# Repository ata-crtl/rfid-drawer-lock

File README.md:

# RFID Drawer Lock

A simple NFC drawer lock built using an ESP32-C3, PN532 NFC reader, and an SG90 servo.

I made this because I wanted a way to lock a drawer without dealing with keys or drilling into furniture , i always seem to lose my keys and lock myself out :( . Just tap an authorised NFC card to unlock it, and tap again to lock it.

**Onshape link:**  
[View the Onshape model](https://cad.onshape.com/documents/10ff17bd51048845f2315452/w/f69d7bc4221a2a5968c6b8fb/e/c57b2dc210264a0650e04200?renderMode=0&uiState=6a241e387df4bc474adedac2)

---

## What it does

- Unlocks a drawer using an NFC card or tag  
- Locks again when the same card is tapped  
- Runs on battery so there are no wires going into the drawer  
- Charges via USB using a TP4056 module  
- Uses red and green LEDs for status  
- Has a physical switch to turn everything off  

---

## How it works

The PN532 reads the UID from an NFC card.

The ESP32 checks if that UID matches the one stored in memory. If it matches, the SG90 servo moves the locking mechanism.

There is also a button for setup so you can register a card easily.

---

## Hardware

### Parts Used

- ESP32 DevKitM1 for the main controller  
- PN532 NFC module for reading cards  
- SG90 servo to move the lock  
- TP4056 module for charging the battery  
- 1S LiPo battery for power  
- Slide switch for power control  
- Red LED for locked or error indication  
- Green LED for power indication  
- 330Ω resistors (x2) for LED current limiting  

---
---

## Building

### 1. Assemble the hardware

- Solder headers and connectors onto the PCB  
- Connect the PN532 module  
- Connect the servo  
- Connect the TP4056 charger  
- Plug in the battery  
- Fit everything into the 3D printed enclosure  

### 2. Upload the firmware

```bash
git clone https://github.com/yourusername/rfid-drawer-lock
cd rfid-drawer-lock
```

Open the project in Arduino IDE or PlatformIO and upload it to the ESP32.

### 3. Register a card

- Hold the register button  
- Tap your NFC card  
- Wait for confirmation  
- The card is now linked to the lock  

---

## Installation

The enclosure is made to stick to the inside of a drawer using strong double-sided tape.

The NFC reader sits behind the drawer front , in a little pocket so you can scan cards from outside.

- Double check battery polarity before connecting  
- Power the servo from 5V, not 3.3V  
- Check PN532 mode 
---

## Future improvements

- Support for multiple authorised cards  
- WiFi logging  
- Battery level monitoring  
- Improved enclosure design  
- Buzzer feedback  
- Mobile app integration

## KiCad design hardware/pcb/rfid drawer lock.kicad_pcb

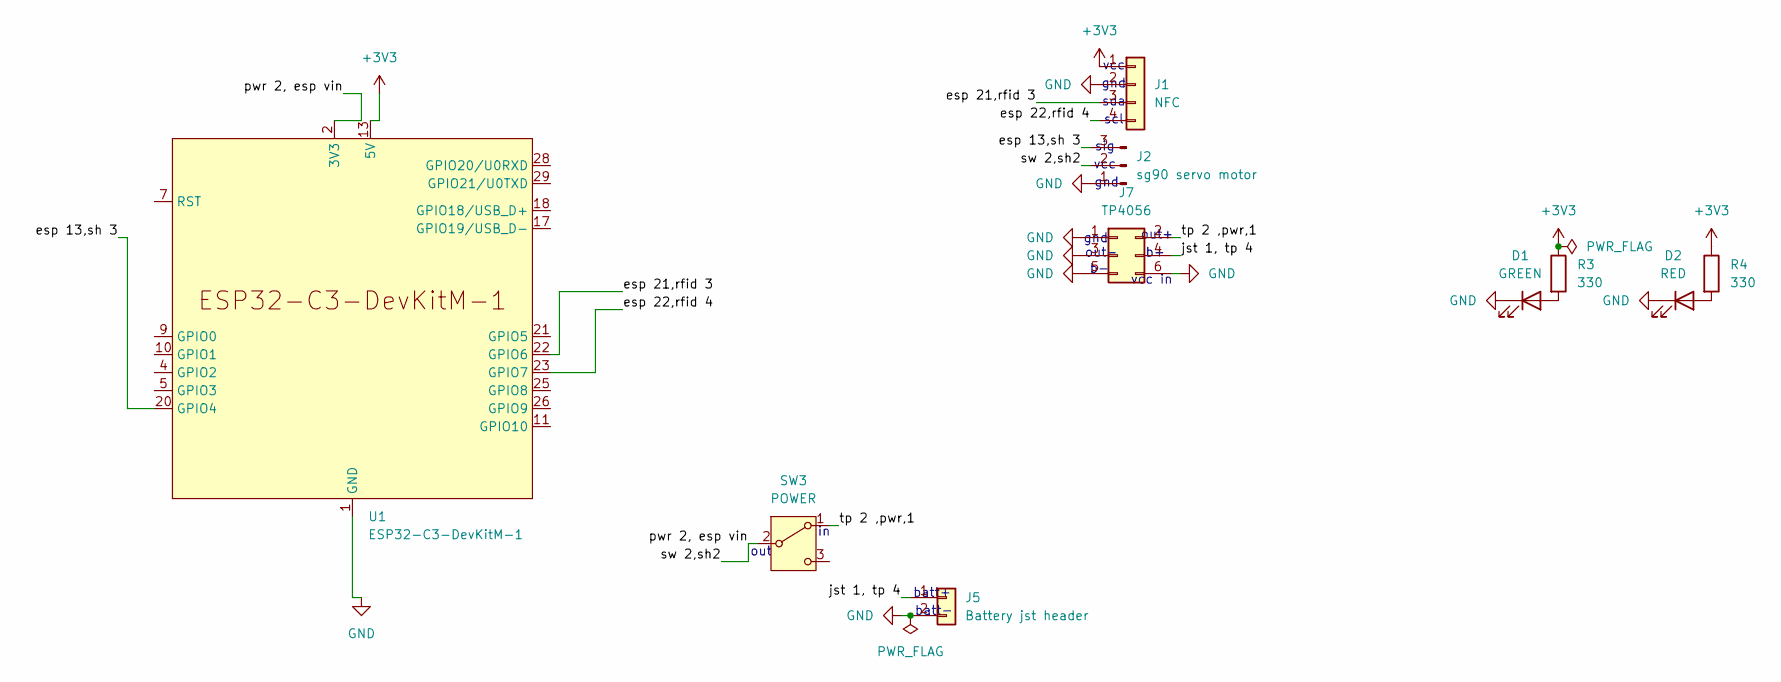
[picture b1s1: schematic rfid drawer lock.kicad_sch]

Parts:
D1: GREEN; LED_D3.0mm
D2: RED; LED_D3.0mm
J1: NFC; PinHeader_1x04_P2.54mm_Vertical
J2: sg90 servo motor; FanPinHeader_1x03_P2.54mm_Vertical
J5: Battery jst header; PinHeader_1x02_P2.54mm_Vertical
J7: TP4056; PinHeader_1x06_P2.54mm_Vertical
R3, R4: 330; R_0805_2012Metric
SW3: POWER; SW_Slide_SPDT_Angled_CK_OS102011MA1Q
U1: ESP32-C3-DevKitM-1

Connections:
3V3: J2.2, SW3.2 (B), U1.2 (3V3), U1.3 (3V3)
+3V3: J1.1, R3.1, R4.1, U1.13 (5V), U1.14 (5V)
/esp 13,sh 3: J2.3, U1.20 (GPIO4)
/esp 21,rfid 3: J1.3, U1.22 (GPIO6)
/esp 22,rfid 4: J1.4, U1.23 (GPIO7)
/jst 1, tp 4: J5.1, J7.4
/tp 2 ,pwr,1: J7.2, SW3.1 (A)
GND: D1.1 (K), D2.1 (K), J1.2, J2.1, J5.2, J7.1, J7.3, J7.5, J7.6, U1.1 (GND), U1.6 (GND), U1.8 (GND), U1.12 (GND), U1.15 (GND), U1.16 (GND), U1.19 (GND), U1.24 (GND), U1.27 (GND), U1.30 (GND)
unnamed: D1.2 (A), R3.2
unnamed: D2.2 (A), R4.2

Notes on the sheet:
sda
out
scl
sig
batt+
vcc
out+
vcc in
gnd
out-
batt-

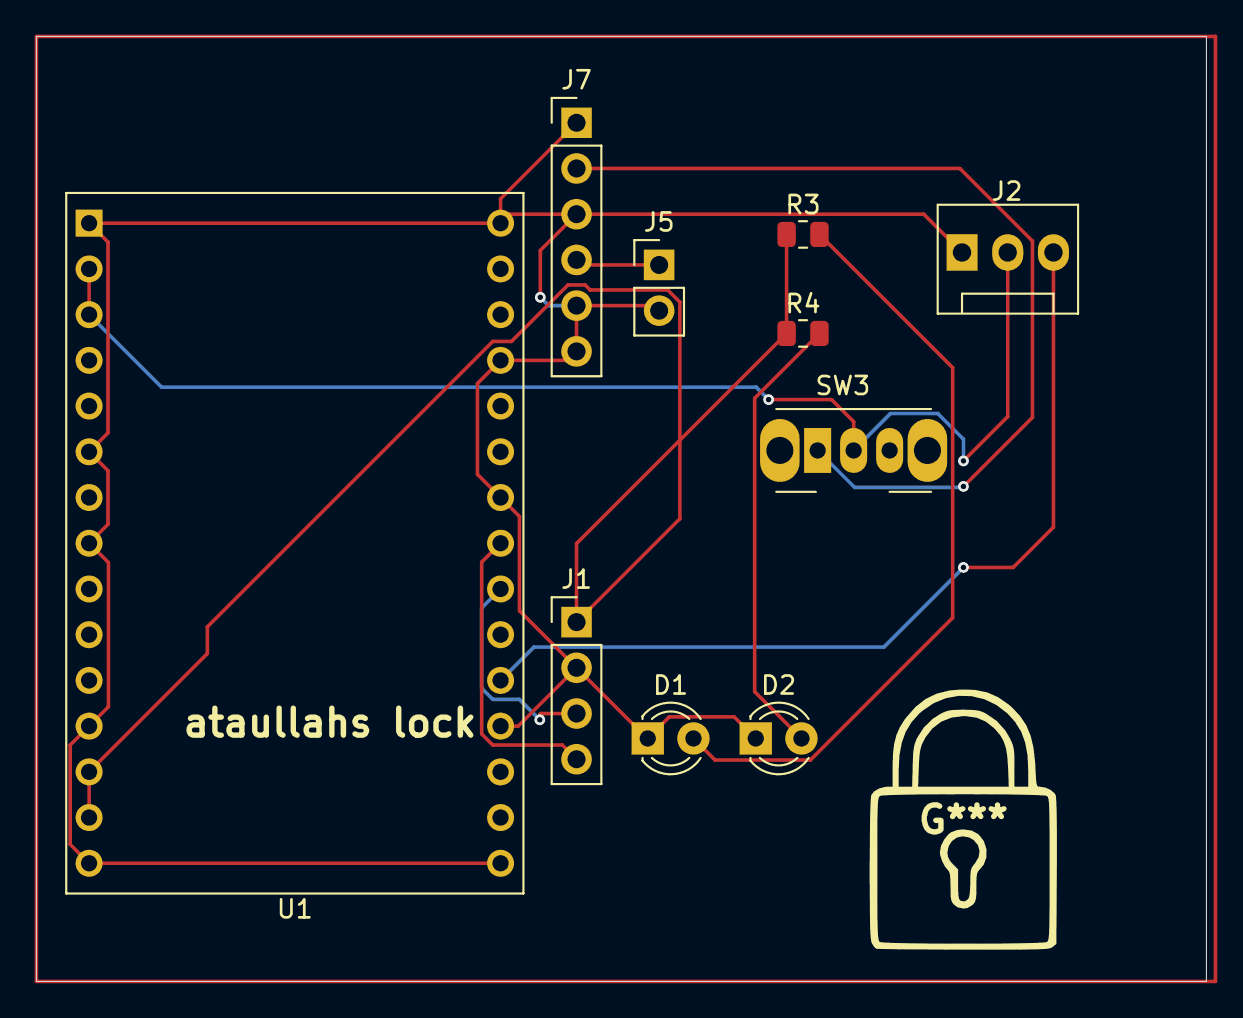
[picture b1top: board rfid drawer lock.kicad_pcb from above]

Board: 2 copper layers, 65.0 x 52.5 mm, 10 parts (0 on the bottom side), 10 nets.

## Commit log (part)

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2026-04-09 Create 3d file
2026-04-11 /code
2026-04-11 Create code
2026-04-11 code
2026-04-11 Rename pn532.py to pn532 code
2026-04-11 Rename main (2).py to main code
2026-04-11 Update and rename 3d model lock.step to 3d model,onshape link
2026-04-11 Create BOM
2026-04-11 Update BOM
2026-04-20 Rename BOM to BOM.csv
2026-04-30 Rename main (2).py to main.py
2026-05-22 Rename Part Studio 3 (1).step to Main frame.step
2026-05-22 Rename Assembly 1 (4).step to Assembly .step
2026-05-26 Create random
2026-05-26 Create rdf
2026-05-30 Rename bom.csv.xlsx to bom.csv
2026-05-30 Rename bom.csv (1).csv to bom.csv
2026-05-30 Create rr
2026-05-31 Create pcb
2026-05-31 Create gh
2026-05-31 Create rnamdo
